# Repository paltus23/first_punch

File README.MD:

This project is intedent to sinmplify start teaching electronics for musical sysntesizers. 

I've already assempled and tested versions 1 and 1.1. 
Version 1.1 works fine but have two issues.
* You should cut track which connects gnd and pin 1 of RV10. Then you should solder small wire between RV10 pin 1 and Vref node.
* There is wrong ploarity of power supply

To use project install Kode Mono font.

There is few photos of ready device v1.1

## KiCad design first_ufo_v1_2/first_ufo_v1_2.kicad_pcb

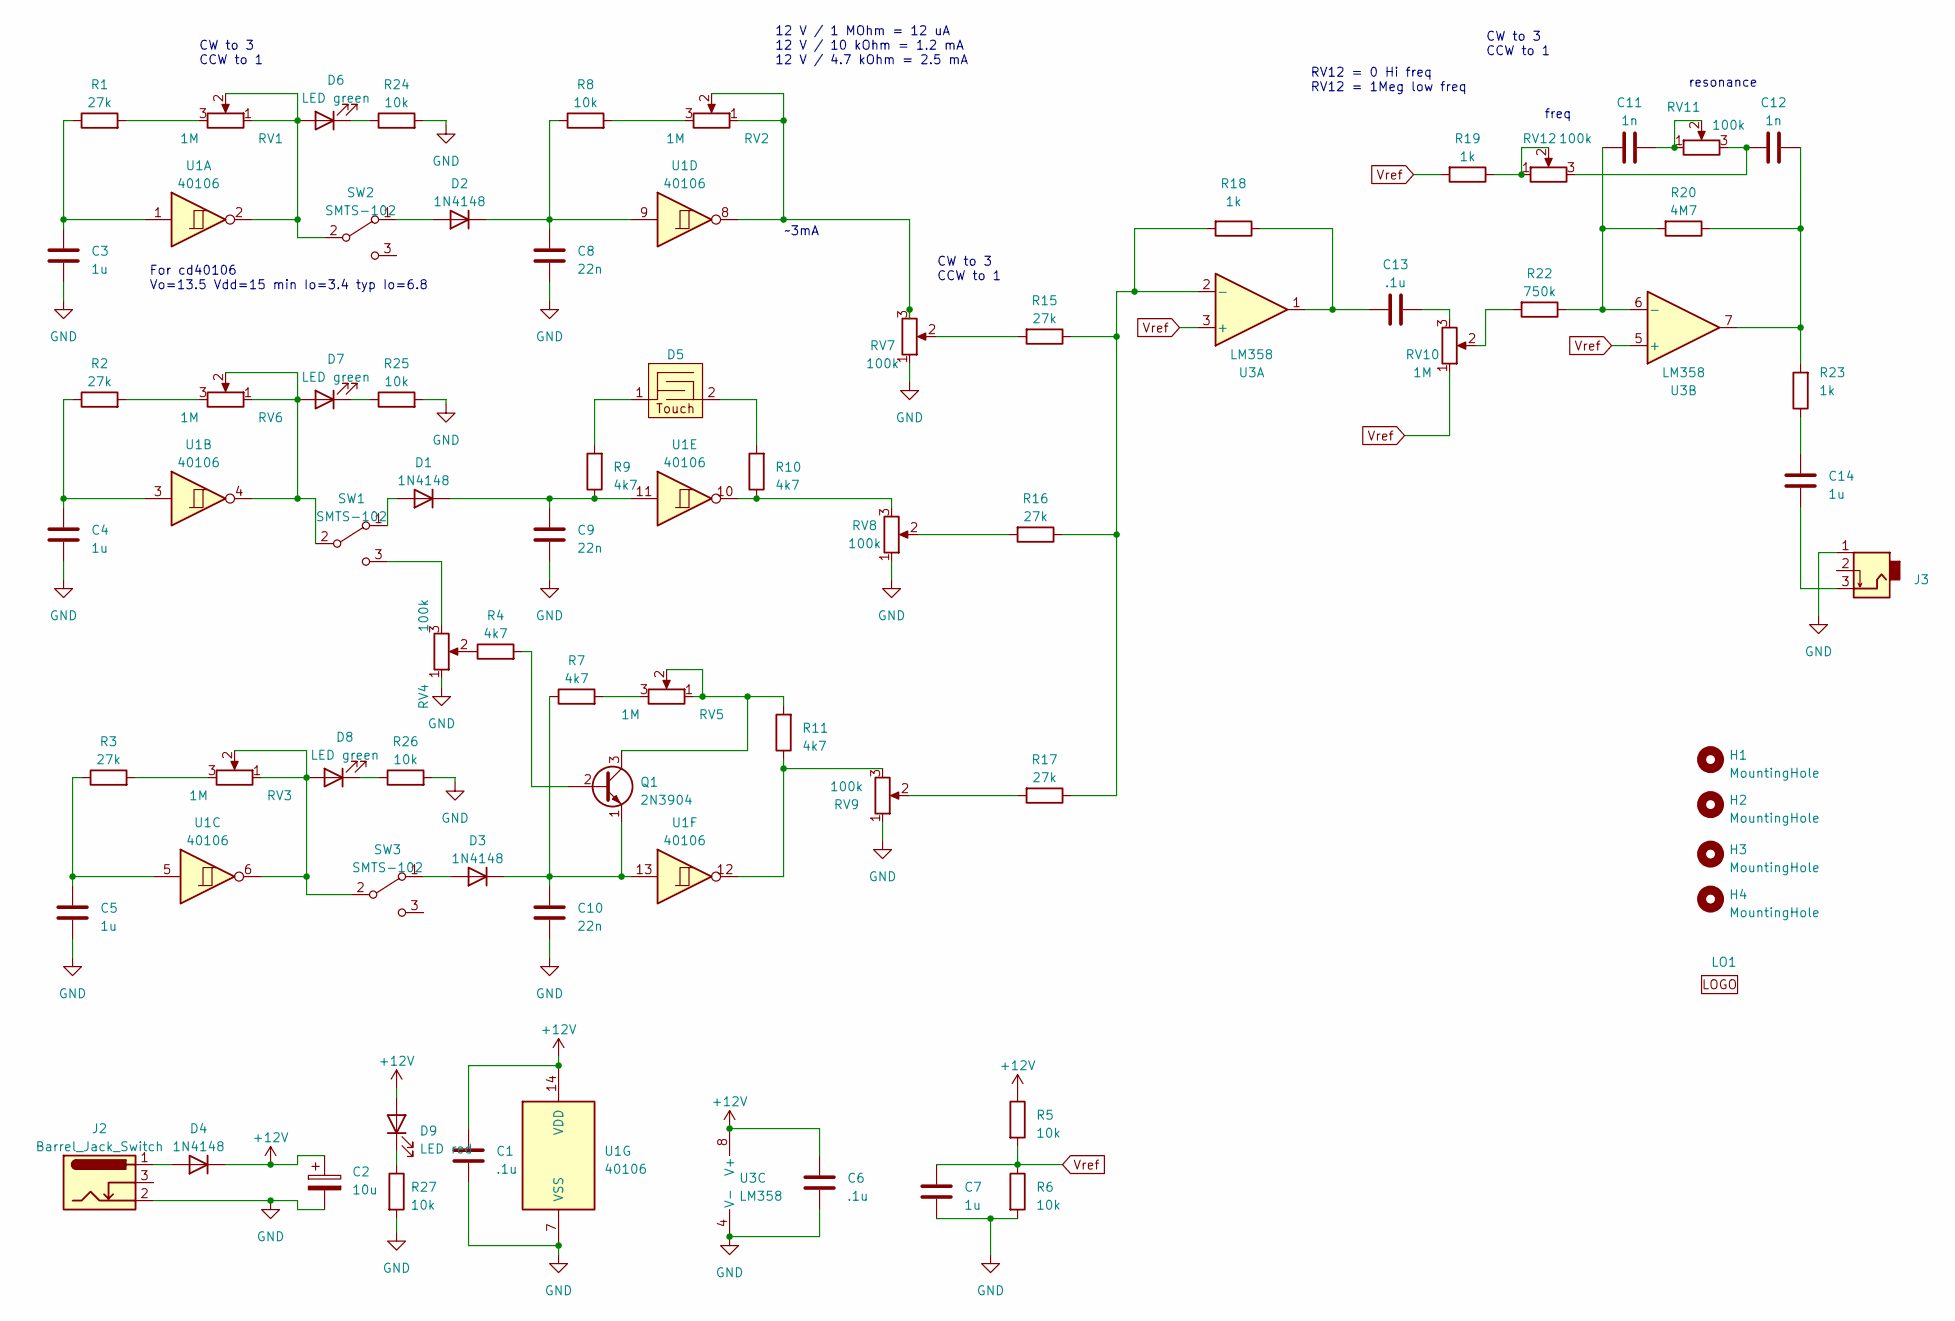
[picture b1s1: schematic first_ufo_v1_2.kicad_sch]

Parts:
C1, C6, C13: .1u; C_Disc_D4.3mm_W1.9mm_P5.00mm
C2: 10u; CP_Radial_D8.0mm_P5.00mm
C3, C4, C5, C7, C14: 1u; C_Disc_D4.3mm_W1.9mm_P5.00mm
C8, C9, C10: 22n; C_Disc_D4.3mm_W1.9mm_P5.00mm
C11, C12: 1n; C_Disc_D4.3mm_W1.9mm_P5.00mm
D1, D2, D3, D4: 1N4148; D_DO-35_SOD27_P10.16mm_Horizontal
D5: tactile pad triangle_1
D6, D7, D8: LED green; LED_D5.0mm
D9: LED red; LED_D5.0mm
H1, H2, H3, H4: MountingHole; MountingHole_3.2mm_M3
J2: Barrel_Jack_Switch; BarrelJack_Wuerth_6941xx301002
J3: PJ-316
LO1: Polarity_Center_Positive_3mm_SilkScreen
Q1: 2N3904; TO-92Flat
R1, R2, R3, R15, R16, R17: 27k; R_Axial_DIN0207_L6.3mm_D2.5mm_P10.16mm_Horizontal
R4, R7, R9, R10, R11: 4k7; R_Axial_DIN0207_L6.3mm_D2.5mm_P10.16mm_Horizontal
R5, R6, R8, R24, R25, R26, R27: 10k; R_Axial_DIN0207_L6.3mm_D2.5mm_P10.16mm_Horizontal
R18, R19, R23: 1k; R_Axial_DIN0207_L6.3mm_D2.5mm_P10.16mm_Horizontal
R20: 4M7; R_Axial_DIN0207_L6.3mm_D2.5mm_P10.16mm_Horizontal
R22: 750k; R_Axial_DIN0207_L6.3mm_D2.5mm_P10.16mm_Horizontal
RV1, RV2, RV3, RV5, RV6, RV10: 1M; Potentiometer_Bourns_PTV09A-1_Single_Vertical
RV4, RV7, RV8, RV9, RV11, RV12: 100k; Potentiometer_Bourns_PTV09A-1_Single_Vertical
SW1, SW2, SW3: SMTS-102
U1: 40106; DIP-14_W7.62mm
U3: LM358; DIP-8_W7.62mm

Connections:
+12V: C1.1, C2.1, C6.1, D4.1 (K), D9.2 (A), R5.1, U1.14 (VDD), U3.8 (V+)
GND: C1.2, C2.2, C3.2, C4.2, C5.2, C6.2, C7.2, C8.2, C9.2, C10.2, J2.2, J3.1, R6.2, R24.2, R25.2, R26.2, R27.2, RV4.1, RV7.1, RV8.1, RV9.1, U1.7 (VSS), U3.4 (V-)
unnamed: C3.1, R1.1, U1.1
unnamed: C4.1, R2.1, U1.3
unnamed: C5.1, R3.1, U1.5
unnamed: C11.2, RV11.1, RV11.2
unnamed: C12.1, RV11.3, RV12.3
unnamed: C12.2, R20.1, R23.2, U3.7
unnamed: C13.1, R18.1, U3.1
unnamed: C13.2, RV10.3
unnamed: C14.1, J3.3
unnamed: C14.2, R23.1
unnamed: D1.2 (A), SW1.1 (A)
unnamed: C9.1, D1.1 (K), R9.1, U1.11
unnamed: D2.2 (A), SW2.1 (A)
unnamed: C8.1, D2.1 (K), R8.1, U1.9
unnamed: D3.2 (A), SW3.1 (A)
unnamed: C10.1, D3.1 (K), Q1.1 (E), R7.1, U1.13
unnamed: D4.2 (A), J2.1
unnamed: D5.1, R9.2
unnamed: D5.2, R10.2
unnamed: D6.2 (A), RV1.1, RV1.2, SW2.2 (B), U1.2
unnamed: D6.1 (K), R24.1
unnamed: D7.2 (A), RV6.1, RV6.2, SW1.2 (B), U1.4
unnamed: D7.1 (K), R25.1
unnamed: D8.2 (A), RV3.1, RV3.2, SW3.2 (B), U1.6
unnamed: D8.1 (K), R26.1
unnamed: D9.1 (K), R27.1
unnamed: Q1.2 (B), R4.2
unnamed: Q1.3 (C), R11.2, RV5.1, RV5.2
unnamed: R1.2, RV1.3
unnamed: R2.2, RV6.3
unnamed: R3.2, RV3.3
unnamed: R4.1, RV4.2
unnamed: R7.2, RV5.3
unnamed: R8.2, RV2.3
unnamed: R10.1, RV8.3, U1.10
unnamed: R11.1, RV9.3, U1.12
unnamed: R15.2, RV7.2
unnamed: R16.2, RV8.2
unnamed: R17.2, RV9.2
unnamed: R19.1, RV12.1, RV12.2
unnamed: R22.2, RV10.2
unnamed: RV2.1, RV2.2, RV7.3, U1.8
unnamed: RV4.3, SW1.3 (C)
unnamed: R15.1, R16.1, R17.1, R18.2, U3.2 (-)
unnamed: C11.1, R20.2, R22.1, U3.6 (-)
Vref: C7.1, R5.2, R6.1, R19.2, RV10.1, U3.3 (+), U3.5 (+)

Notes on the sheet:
RV12 = 0 Hi freq RV12 = 1Meg low freq
resonance
CW to 3 CCW to 1
12 V / 1 MOhm = 12 uA 12 V / 10 kOhm = 1.2 mA 12 V / 4.7 kOhm = 2.5 mA
~3mA
For cd40106 Vo=13.5 Vdd=15 min Io=3.4 typ Io=6.8
freq

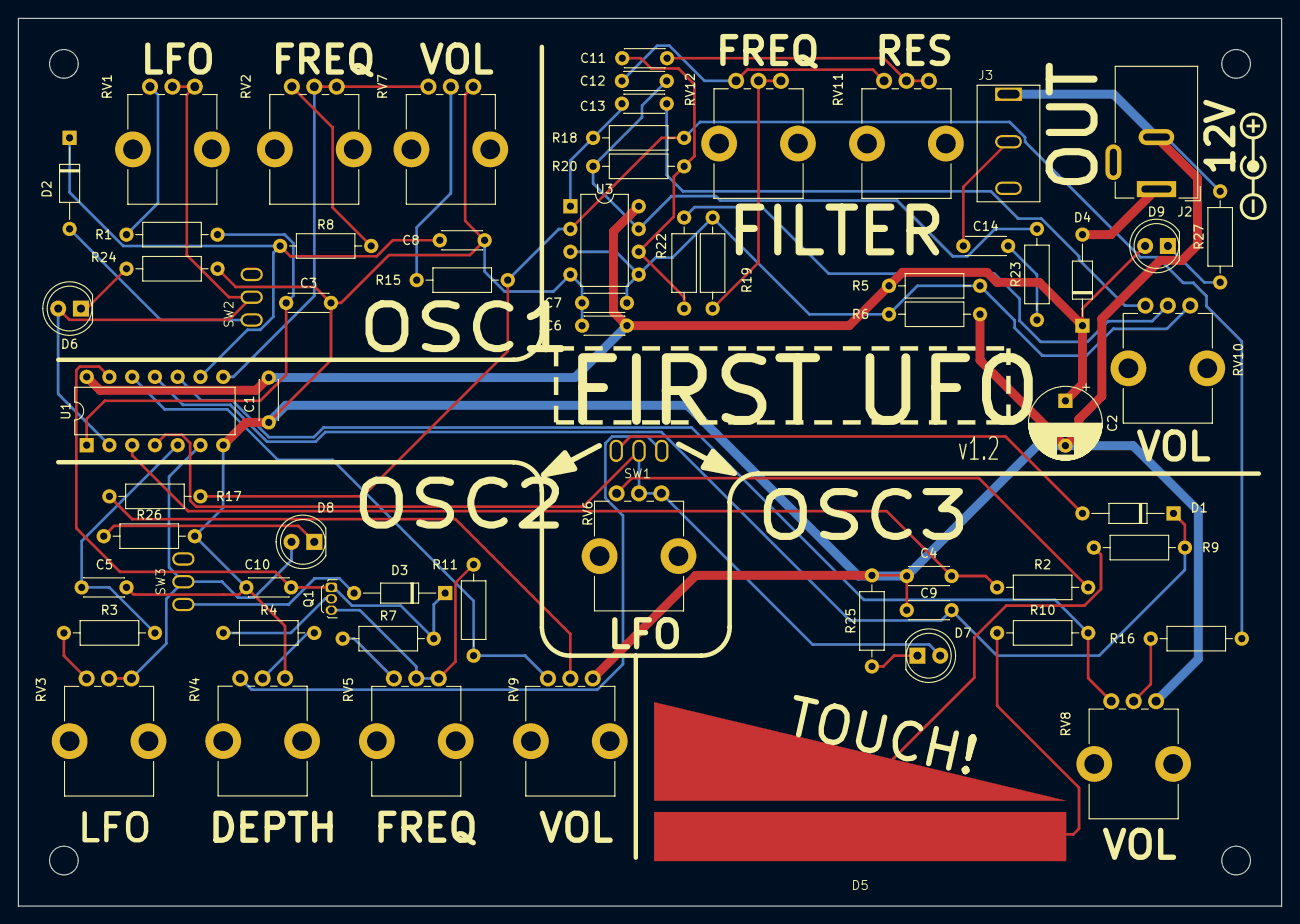
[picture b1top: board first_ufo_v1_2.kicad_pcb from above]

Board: 2 copper layers, 141.0 x 99.1 mm, 71 parts (0 on the bottom side), 48 nets.

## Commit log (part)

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2023-11-06 init
2023-11-06 gitignore
2023-12-14 Finish circuit and pcb
2023-12-14 add paints move ref resistors
2023-12-14 change AudioJack to PJ-316 Separate leds into green and red
2023-12-14 add mounting holes for M3 screws
2023-12-17 add text - Ver1 - symbol for power supply - title - text on rear
2024-01-30 add coments on sch
2024-04-11 move to directory
2024-04-11 add gitignore
2024-04-11 add v1_1
2024-04-13 edit R15 16 17 to 27k for do not affect on freq in max volume edit RV7 8 9 for better control of volume. coz it use volatge divider now change filter for better control and range fix adder circuit. m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
2024-05-05 no message
2024-06-20 move lines
2024-06-25 many many changes
